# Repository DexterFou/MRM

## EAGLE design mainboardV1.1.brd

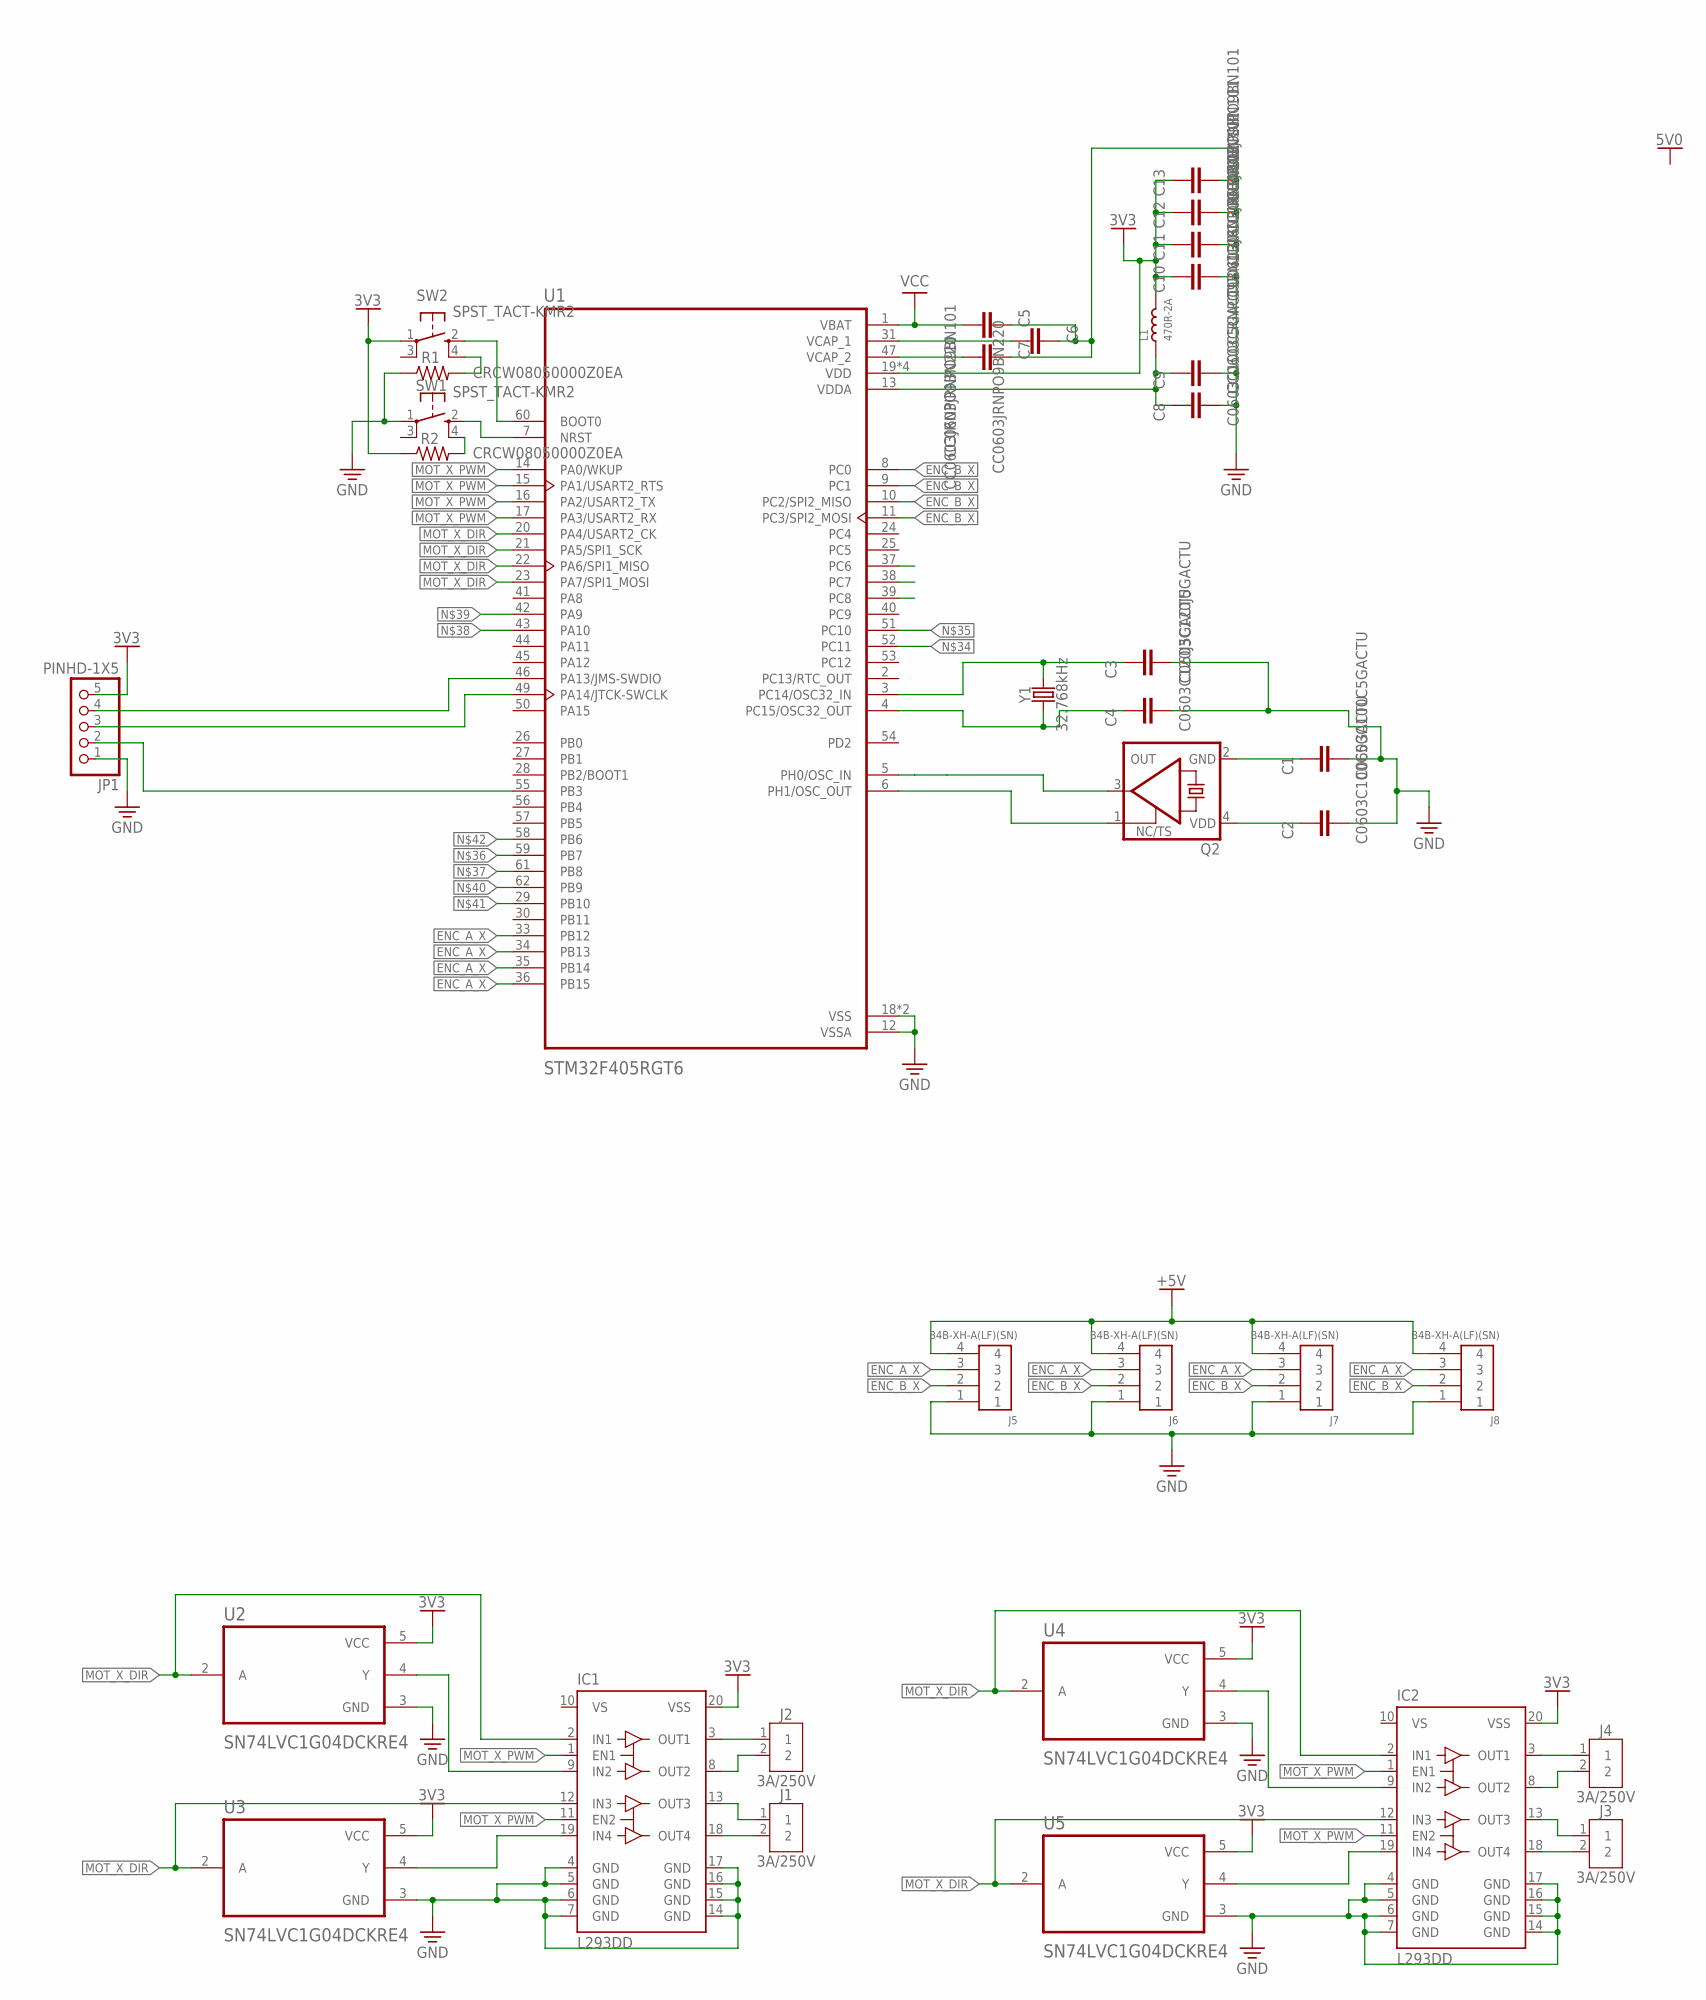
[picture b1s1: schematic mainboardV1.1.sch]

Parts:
C1, C2, C8: C0603C100C5GACTU; CAP_0603
C3, C4: C0603C120J5GACTU; CAP_0603
C5, C10, C11, C12, C13: CC0603JRNPO9BN101; CAP_0603
C6, C7: CC0603JRNPO9BN220; CAP_0603
C9: CC0603CRNPO9BN1R0; CAP_0603
IC1, IC2: L293DD; SO20
J1, J2, J3, J4: 3A/250V; B2B-XH-A
J5, J6, J7, J8: B4B-XH-A(LF)(SN)
JP1: PINHD-1X5; 1X05
L1: 470R-2A; L0805
Q2: KXO-PXO/XO-V96; 3.2X2.5_KXO-V96
R1, R2: CRCW08050000Z0EA; RES_0805
SW1, SW2: SPST_TACT-KMR2; KMR2
U1: STM32F405RGT6; QFP50P1200X1200X160-64N
U2, U3, U4, U5: SN74LVC1G04DCKRE4; SOT65P210X110-5N
Y1: 32.768kHz; CRYSTAL-SMD-3.2X1.5MM

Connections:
3V3: C10.1, C11.1, C12.1, C13.1, IC1.20 (VSS), IC2.20 (VSS), JP1.5, L1.2, R2.1, SW2.1, U1.19 (VDD), U1.32 (VDD), U1.48 (VDD), U1.64 (VDD), U2.5 (VCC), U3.5 (VCC), U4.5 (VCC), U5.5 (VCC)
+5V: J5.4, J6.4, J7.4, J8.4
ENC_A_X: J5.3, J6.3, J7.3, J8.3, U1.33 (PB12), U1.34 (PB13), U1.35 (PB14), U1.36 (PB15)
ENC_B_X: J5.2, J6.2, J7.2, J8.2, U1.8 (PC0), U1.9 (PC1), U1.10 (PC2/SPI2_MISO), U1.11 (PC3/SPI2_MOSI)
GND: C1.2, C2.2, C3.2, C4.2, C5.1, C6.1, C7.1, C8.2, C9.2, C10.2, C11.2, C12.2, C13.2, IC1.4 (GND), IC1.5 (GND), IC1.6 (GND), IC1.7 (GND), IC1.14 (GND), IC1.15 (GND), IC1.16 (GND), IC1.17 (GND), IC2.4 (GND), IC2.5 (GND), IC2.6 (GND), IC2.7 (GND), IC2.14 (GND), IC2.15 (GND), IC2.16 (GND), IC2.17 (GND), J5.1, J6.1, J7.1, J8.1, JP1.1, R1.1, SW1.1, U1.12 (VSSA), U1.18 (VSS), U1.63 (VSS), U2.3 (GND), U3.3 (GND), U4.3 (GND), U5.3 (GND)
MOT_X_DIR: IC1.2 (IN1), IC1.12 (IN3), IC2.2 (IN1), IC2.12 (IN3), U1.20 (PA4/USART2_CK), U1.21 (PA5/SPI1_SCK), U1.22 (PA6/SPI1_MISO), U1.23 (PA7/SPI1_MOSI), U2.2 (A), U3.2 (A), U4.2 (A), U5.2 (A)
MOT_X_PWM: IC1.1 (EN1), IC1.11 (EN2), IC2.1 (EN1), IC2.11 (EN2), U1.14 (PA0/WKUP), U1.15 (PA1/USART2_RTS), U1.16 (PA2/USART2_TX), U1.17 (PA3/USART2_RX)
unnamed: Q2.3 (OUT), U1.5 (PH0/OSC_IN)
unnamed: Q2.1 (TS), U1.6 (PH1/OSC_OUT)
unnamed: C4.1, U1.4 (PC15/OSC32_OUT), Y1.P$1 (1)
unnamed: JP1.4, U1.46 (PA13/JMS-SWDIO)
unnamed: JP1.3, U1.49 (PA14/JTCK-SWCLK)
unnamed: JP1.2, U1.55 (PB3)
unnamed: IC1.19 (IN4), U3.4 (Y)
unnamed: C6.2, U1.31 (VCAP_1)
unnamed: C8.1, C9.1, L1.1, U1.13 (VDDA)
unnamed: SW2.2 (S), U1.60 (BOOT0)
unnamed: SW1.2 (S), U1.7 (NRST)
unnamed: C7.2, U1.47 (VCAP_2)
unnamed: R1.2, SW2.4 (S1)
unnamed: R2.2, SW1.4 (S1)
unnamed: C3.1, U1.3 (PC14/OSC32_IN), Y1.P$2 (2)
unnamed: C1.1, Q2.2 (GND)
unnamed: C2.1, Q2.4 (VDD)
unnamed: IC1.9 (IN2), U2.4 (Y)
unnamed: IC1.13 (OUT3), J1.1
unnamed: IC1.18 (OUT4), J1.2
unnamed: IC1.8 (OUT2), J2.2
unnamed: IC1.3 (OUT1), J2.1
unnamed: IC2.19 (IN4), U5.4 (Y)
unnamed: IC2.9 (IN2), U4.4 (Y)
unnamed: IC2.13 (OUT3), J3.1
unnamed: IC2.18 (OUT4), J3.2
unnamed: IC2.8 (OUT2), J4.2
unnamed: IC2.3 (OUT1), J4.1
VCC: C5.2, U1.1 (VBAT)
VS: IC1.10 (VS), IC2.10 (VS)

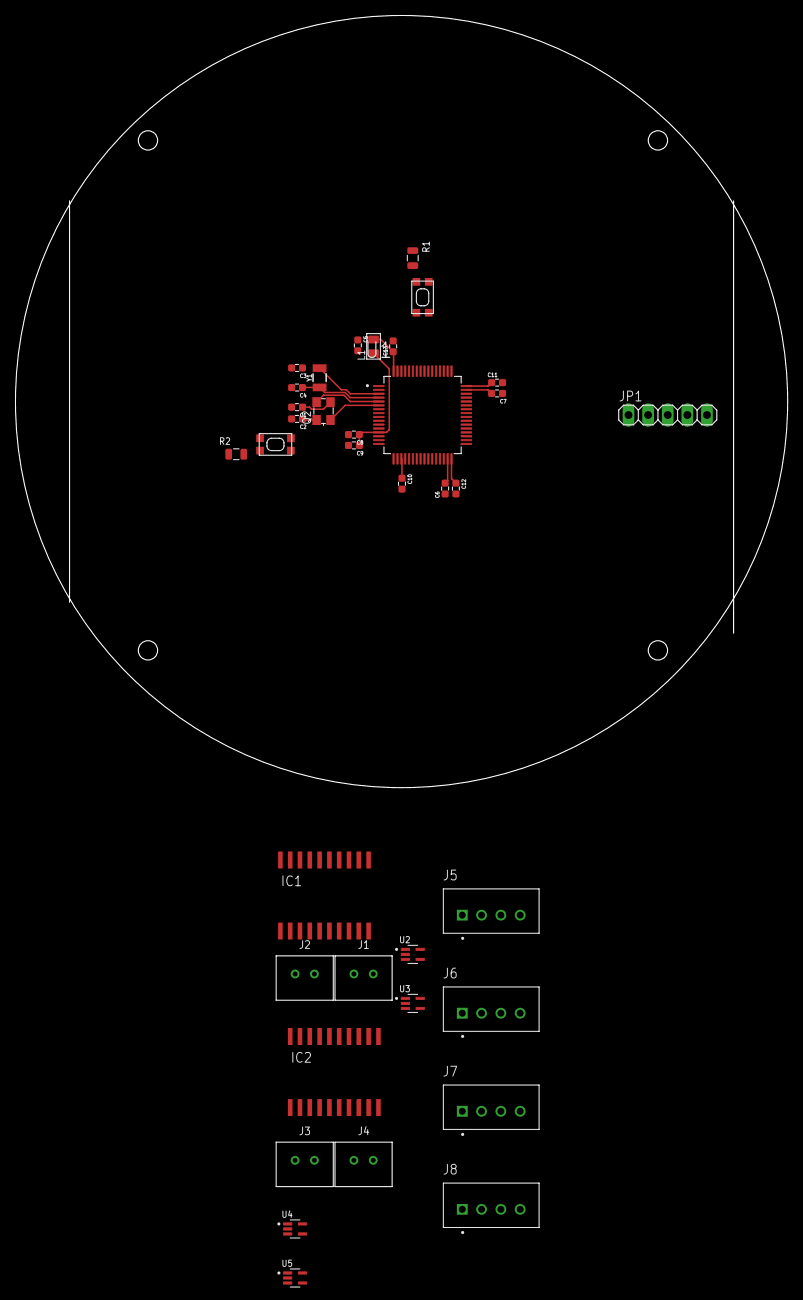
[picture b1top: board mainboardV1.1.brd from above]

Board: 2 copper layers, 100.0 x 100.0 mm, 36 parts (0 on the bottom side), 37 nets.

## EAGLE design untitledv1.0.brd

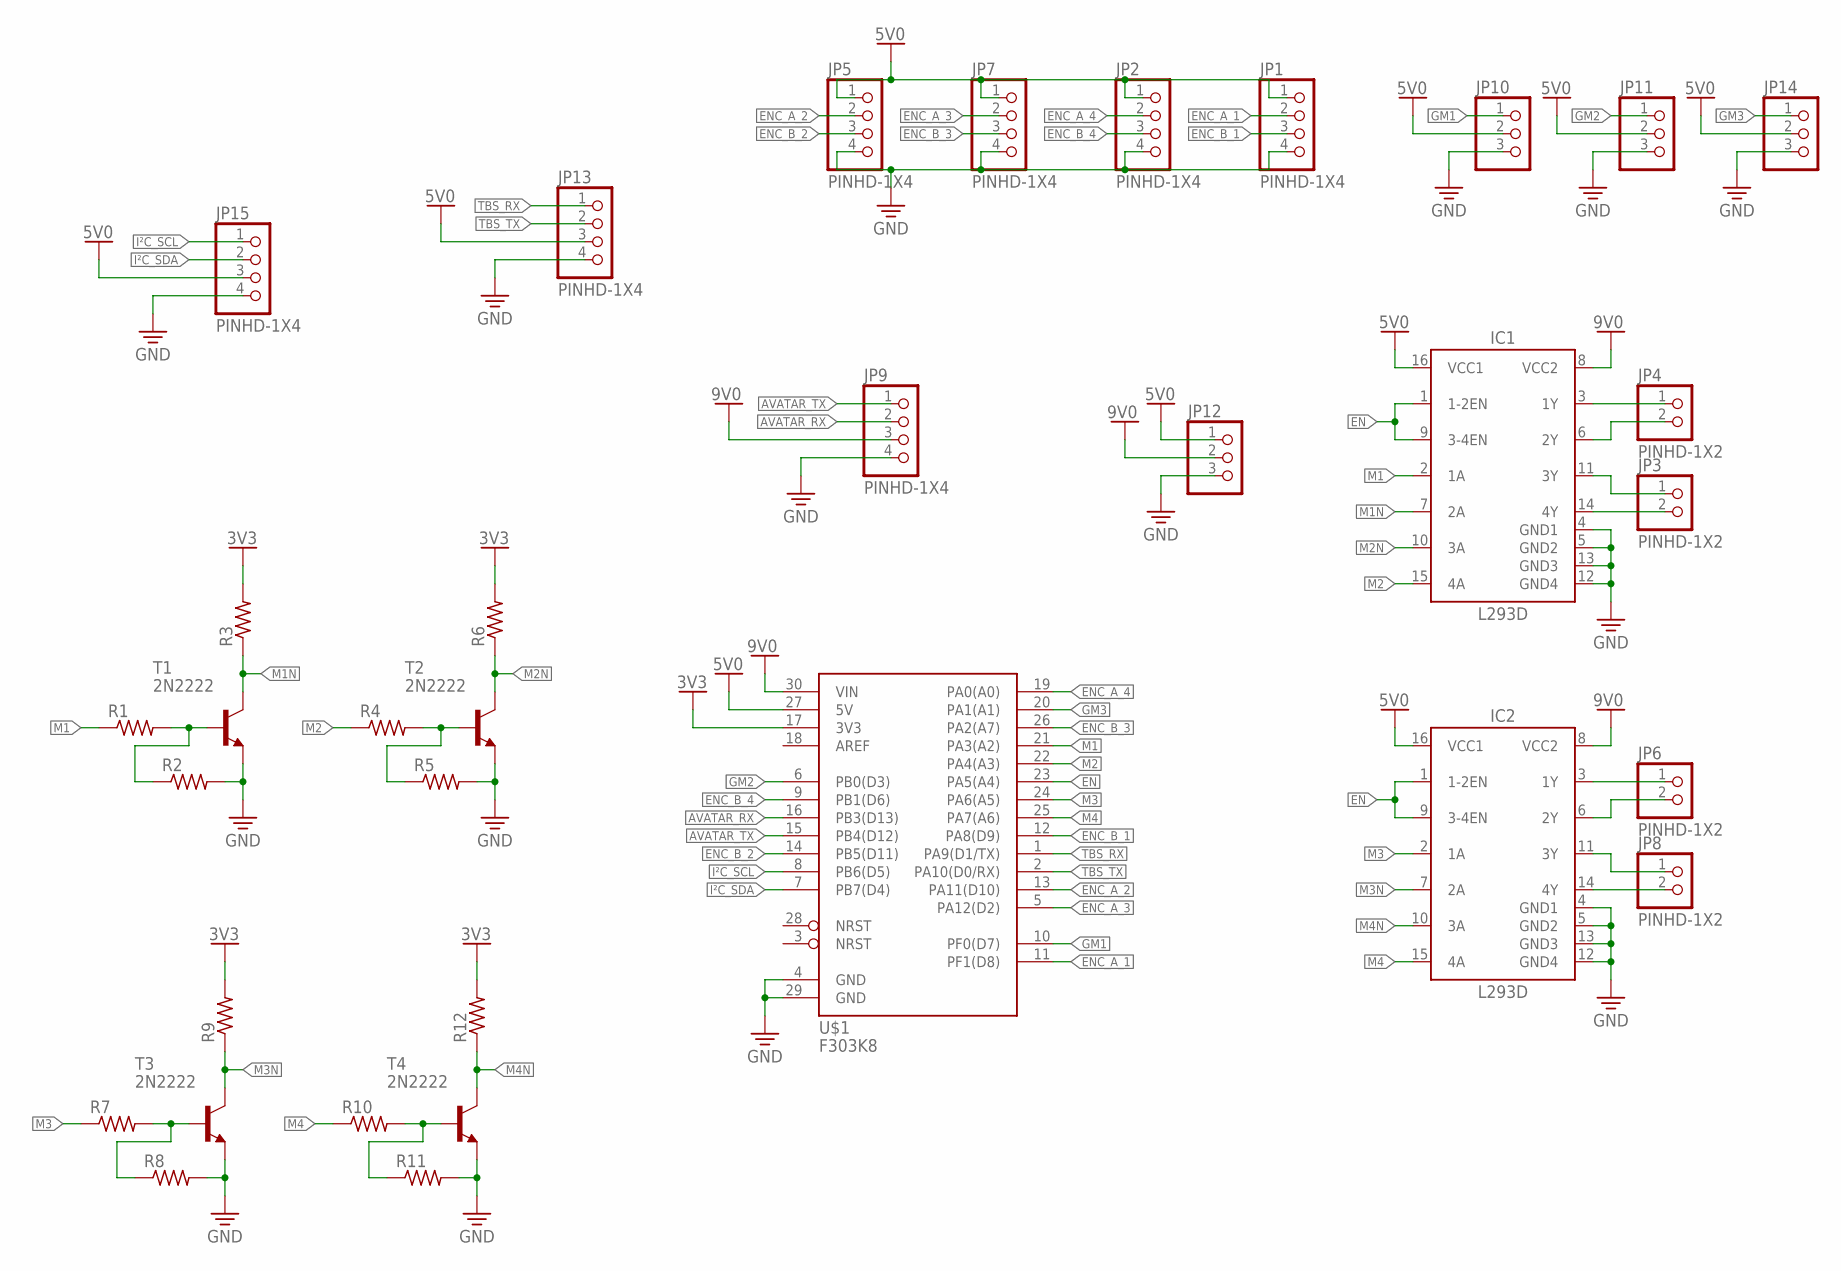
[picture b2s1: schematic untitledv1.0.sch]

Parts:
IC1, IC2: L293D; DIP762W53P254L1969H508Q16B
JP1, JP2, JP5, JP7, JP9, JP13, JP15: PINHD-1X4; 1X04
JP3, JP4, JP6, JP8: PINHD-1X2; 1X02
JP10, JP11, JP12, JP14: PINHD-1X3; 1X03
R1, R2, R3, R4, R5, R6, R7, R8, R9, R10, R11, R12: R-US_0204/2V; 0204V
T1, T2, T3, T4: 2N2222; TO92-EBC-OVAL
U$1: F303K8; NUCLEO_F303K8-V2

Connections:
3V3: R3.2, R6.2, R9.2, R12.2, U$1.17 (3V3)
5V0: IC1.16 (VCC1), IC2.16 (VCC1), JP1.1, JP2.1, JP5.1, JP7.1, JP10.2, JP11.2, JP12.1, JP13.3, JP14.2, JP15.3, U$1.27 (5V)
9V0: IC1.8 (VCC2), IC2.8 (VCC2), JP9.3, JP12.2, U$1.30 (VIN)
AVATAR_RX: JP9.2, U$1.16 (PB3(D13))
AVATAR_TX: JP9.1, U$1.15 (PB4(D12))
EN: IC1.1 (1-2EN), IC1.9 (3-4EN), IC2.1 (1-2EN), IC2.9 (3-4EN), U$1.23 (PA5(A4))
ENC_A_1: JP1.2, U$1.11 (PF1(D8))
ENC_A_2: JP5.2, U$1.13 (PA11(D10))
ENC_A_3: JP7.2, U$1.5 (PA12(D2))
ENC_A_4: JP2.2, U$1.19 (PA0(A0))
ENC_B_1: JP1.3, U$1.12 (PA8(D9))
ENC_B_2: JP5.3, U$1.14 (PB5(D11))
ENC_B_3: JP7.3, U$1.26 (PA2(A7))
ENC_B_4: JP2.3, U$1.9 (PB1(D6))
GM1: JP10.1, U$1.10 (PF0(D7))
GM2: JP11.1, U$1.6 (PB0(D3))
GM3: JP14.1, U$1.20 (PA1(A1))
GND: IC1.4 (GND1), IC1.5 (GND2), IC1.12 (GND4), IC1.13 (GND3), IC2.4 (GND1), IC2.5 (GND2), IC2.12 (GND4), IC2.13 (GND3), JP1.4, JP2.4, JP5.4, JP7.4, JP9.4, JP10.3, JP11.3, JP12.3, JP13.4, JP14.3, JP15.4, R2.2, R5.2, R8.2, R11.2, T1.E, T2.E, T3.E, T4.E, U$1.4 (GND), U$1.29 (GND)
I²C_SCL: JP15.1, U$1.8 (PB6(D5))
I²C_SDA: JP15.2, U$1.7 (PB7(D4))
M1: IC1.2 (1A), R1.1, U$1.21 (PA3(A2))
M1N: IC1.7 (2A), R3.1, T1.C
M2: IC1.15 (4A), R4.1, U$1.22 (PA4(A3))
M2N: IC1.10 (3A), R6.1, T2.C
M3: IC2.2 (1A), R7.1, U$1.24 (PA6(A5))
M3N: IC2.7 (2A), R9.1, T3.C
M4: IC2.15 (4A), R10.1, U$1.25 (PA7(A6))
M4N: IC2.10 (3A), R12.1, T4.C
unnamed: IC1.14 (4Y), JP3.2
unnamed: IC1.11 (3Y), JP3.1
unnamed: IC1.6 (2Y), JP4.2
unnamed: IC1.3 (1Y), JP4.1
unnamed: IC2.3 (1Y), JP6.1
unnamed: IC2.6 (2Y), JP6.2
unnamed: IC2.11 (3Y), JP8.1
unnamed: IC2.14 (4Y), JP8.2
unnamed: R1.2, R2.1, T1.B
unnamed: R4.2, R5.1, T2.B
unnamed: R7.2, R8.1, T3.B
unnamed: R10.2, R11.1, T4.B
TBS_RX: JP13.1, U$1.1 (PA9(D1/TX))
TBS_TX: JP13.2, U$1.2 (PA10(D0/RX))

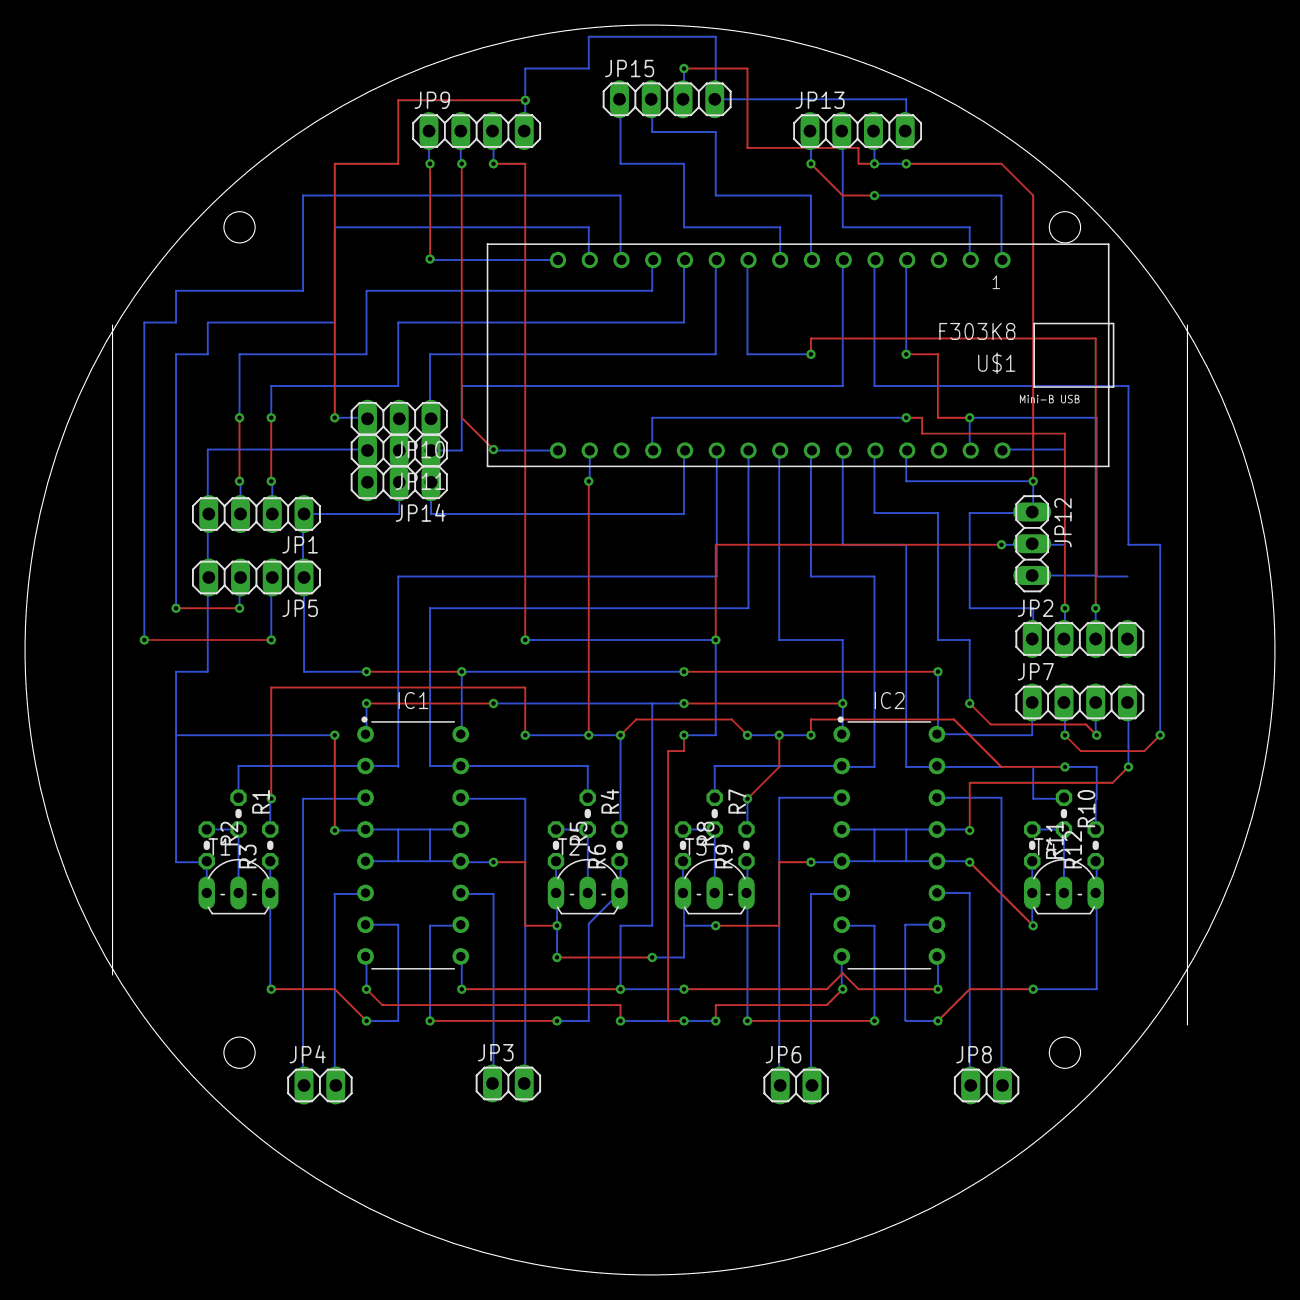
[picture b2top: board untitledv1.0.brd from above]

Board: 2 copper layers, 100.0 x 100.0 mm, 34 parts (0 on the bottom side), 42 nets.

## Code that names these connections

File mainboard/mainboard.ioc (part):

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Mcu.Name=STM32F405RGTx
Mcu.Package=LQFP64
Mcu.UserName=STM32F405RGTx
PA0-WKUP.GPIOParameters=GPIO_Label
PA0-WKUP.GPIO_Label=MOT_X_PWM
PA0-WKUP.Signal=S_TIM2_CH1_ETR
PA1.GPIOParameters=GPIO_Label
PA1.GPIO_Label=MOT_X_PWM
PA1.Signal=S_TIM2_CH2
PA10.Mode=Asynchronous
PA10.Signal=USART1_RX
PA13.Mode=Trace_Asynchronous_SW
PA13.Signal=SYS_JTMS-SWDIO
PA14.Mode=Trace_Asynchronous_SW
PA14.Signal=SYS_JTCK-SWCLK
PA2.GPIOParameters=GPIO_Label
PA2.GPIO_Label=MOT_X_PWM
PA2.Signal=S_TIM2_CH3
PA3.GPIOParameters=GPIO_Label
PA3.GPIO_Label=MOT_X_PWM
PA3.Signal=S_TIM2_CH4
PA4.GPIOParameters=GPIO_Label
PA4.GPIO_Label=MOT_X_DIR
PA4.Signal=GPIO_Output
PA5.GPIOParameters=GPIO_Label
PA5.GPIO_Label=MOT_X_DIR
PA5.Signal=GPIO_Output
PA6.GPIOParameters=GPIO_Label
PA6.GPIO_Label=MOT_X_DIR
PA6.Signal=GPIO_Output
PA7.GPIOParameters=GPIO_Label
PA7.GPIO_Label=MOT_X_DIR
PA7.Signal=GPIO_Output
PA9.Mode=Asynchronous
PA9.Signal=USART1_TX
PB10.Mode=I2C
PB10.Signal=I2C2_SCL
PB11.Mode=I2C
PB11.Signal=I2C2_SDA
PB12.GPIOParameters=GPIO_Label
PB12.GPIO_Label=ENC_A_X
PB12.Signal=GPXTI12
PB13.GPIOParameters=GPIO_Label
PB13.GPIO_Label=ENC_A_X
PB13.Signal=GPXTI13
PB14.GPIOParameters=GPIO_Label
PB14.GPIO_Label=ENC_A_X
PB14.Signal=GPXTI14
PB15.GPIOParameters=GPIO_Label
PB15.GPIO_Label=ENC_A_X
PB15.Signal=GPXTI15
PB3.Mode=Trace_Asynchronous_SW
PB3.Signal=SYS_JTDO-SWO
PB6.Mode=I2C
PB6.Signal=I2C1_SCL
PB7.Mode=I2C
PB7.Signal=I2C1_SDA
PC0.GPIOParameters=GPIO_Label
PC0.GPIO_Label=ENC_B_X
PC0.Signal=GPIO_Input
PC1.GPIOParameters=GPIO_Label
PC1.GPIO_Label=ENC_B_X
PC1.Signal=GPIO_Input
PC10.Mode=Asynchronous
PC10.Signal=USART3_TX
PC11.Mode=Asynchronous
PC11.Signal=USART3_RX
PC14-OSC32_IN.Mode=LSE-External-Oscillator
PC14-OSC32_IN.Signal=RCC_OSC32_IN
PC15-OSC32_OUT.Mode=LSE-External-Oscillator
PC15-OSC32_OUT.Signal=RCC_OSC32_OUT
PC2.GPIOParameters=GPIO_Label
PC2.GPIO_Label=ENC_B_X
PC2.Signal=GPIO_Input
PC3.GPIOParameters=GPIO_Label
PC3.GPIO_Label=ENC_B_X
PC3.Signal=GPIO_Input
PC6.GPIOParameters=GPIO_Label
PC6.GPIO_Label=LIDAR_TX
PC6.Mode=Asynchronous
PC6.Signal=USART6_TX
PC7.GPIOParameters=GPIO_Label
PC7.GPIO_Label=LIDAR_RX
PC7.Mode=Asynchronous
PC7.Signal=USART6_RX
PC8.GPIOParameters=GPIO_Label
PC8.GPIO_Label=LIDAR_MOT
PC8.Signal=S_TIM3_CH3
PH0-OSC_IN.Mode=HSE-External-Oscillator
PH0-OSC_IN.Signal=RCC_OSC_IN
PH1-OSC_OUT.Mode=HSE-External-Oscillator
PH1-OSC_OUT.Signal=RCC_OSC_OUT
RCC.HSE_VALUE=8000000
RCC.SYSCLKFreq_VALUE=168000000
RCC.SYSCLKSource=RCC_SYSCLKSOURCE_PLLCLK
board=custom

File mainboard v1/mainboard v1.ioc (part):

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Mcu.Name=STM32F303K(6-8)Tx
Mcu.Package=LQFP32
Mcu.UserName=STM32F303K8Tx
PA0.Signal=GPXTI0
PA11.Signal=GPXTI11
PA12.Signal=GPXTI12
PA13.GPIOParameters=GPIO_Label
PA13.GPIO_Label=SWDIO
PA13.Mode=Serial_Wire
PA13.Signal=SYS_JTMS-SWDIO
PA14.GPIOParameters=GPIO_Label
PA14.GPIO_Label=SWCLK
PA14.Mode=Serial_Wire
PA14.Signal=SYS_JTCK-SWCLK
PA15.GPIOParameters=GPIO_Label
PA15.GPIO_Label=VCP_RX
PA15.Mode=Asynchronous
PA15.Signal=USART2_RX
PA2.GPIOParameters=GPIO_Label
PA2.GPIO_Label=VCP_TX
PA2.Mode=Asynchronous
PA2.Signal=USART2_TX
PA3.Signal=S_TIM2_CH4
PA4.Signal=S_TIM3_CH2
PA5.Signal=GPIO_Output
PA6.Signal=S_TIM3_CH1
PA7.Mode=PWM Generation1 CH1N
PA7.Signal=TIM1_CH1N
PA8.Signal=GPIO_Input
PB1.Signal=GPIO_Input
PB5.Signal=GPIO_Input
PF0\ /\ OSC_IN.GPIOParameters=GPIO_Label
PF0\ /\ OSC_IN.GPIO_Label=MCO
PF0\ /\ OSC_IN.Mode=HSE-External-Clock-Source
PF0\ /\ OSC_IN.Signal=RCC_OSC_IN
PF1\ /\ OSC_OUT.Signal=GPXTI1
RCC.HSEPLLFreq_Value=8000000
RCC.HSE_VALUE=8000000
RCC.SYSCLKFreq_VALUE=64000000
RCC.SYSCLKSourceVirtual=RCC_SYSCLKSOURCE_PLLCLK
board=NUCLEO-F303K8
boardIOC=true

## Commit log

2024-07-31 datasheet and eagle proj
2024-08-08 pcb finished
2024-08-24 some pcb dev
2024-09-22 123456789

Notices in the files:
parts and their libraries:
SparkFun-Clocks: Licensing: Creative Commons ShareAlike 4.0 International - https://creativecommons.org/licenses/by-sa/4.0
crystal-geyer_V1_0: Copyright: Geyer-Electronic
